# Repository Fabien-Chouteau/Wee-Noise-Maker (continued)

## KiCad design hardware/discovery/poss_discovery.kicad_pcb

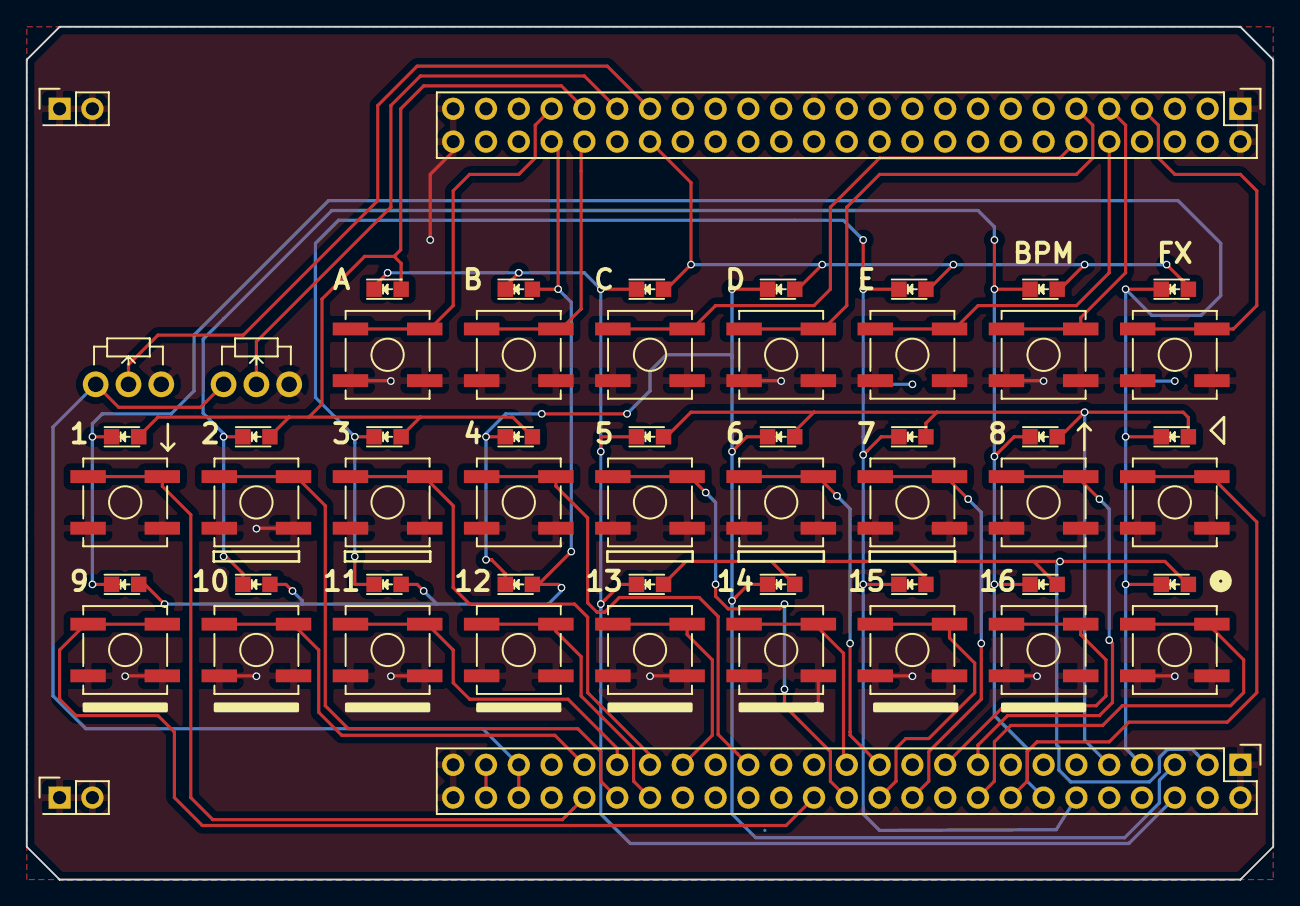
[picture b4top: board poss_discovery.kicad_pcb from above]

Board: 2 copper layers, 96.5 x 66.0 mm, 56 parts (0 on the bottom side), 41 nets.

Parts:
D1, D2, D3, D4, D5, D6, D7, D8, D9, D10, D11, D12, D13, D14, D15, D16, D17, D18, D19, D20, D21, D22, D23, D24, D25: LED; LED_0805
J1, J5: HEADER_2; Pin_Header_Straight_2x01
J2, J3: HEADER_25x2; Pin_Header_Straight_2x25
Play1, Play2: SW_PUSH; SW_SPST_B3SL-1002P
RV1, RV2: POT; Potentiometer_WirePads_Small
SW1, SW2, SW3, SW4, SW5, SW6, SW7, SW8, SW9, SW10, SW11, SW12, SW13, SW14, SW15, SW16, SW17, SW18, SW19, SW20, SW21, SW22: SW_PUSH; SW_SPST_B3SL-1002P
Write1: SW_PUSH; SW_SPST_B3SL-1002P

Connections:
/3V: J3.45, J3.46, RV1.1, RV2.1
/5V: J3.47, J3.48
/B1: J3.42, SW1.1
/B2: J3.40, SW2.1
/B3: J3.37, SW3.1
/B4: J3.31, SW4.1
/B5: J3.26, SW5.1
/B6: J3.23, SW6.1
/B7: J3.22, SW7.1
/B8: J3.17, SW8.1
/B9: J3.28, SW9.1
/B10: J3.41, SW10.1
/B11: J3.39, SW11.1
/B12: J3.38, SW12.1
/B13: J3.35, SW13.1
/B14: J3.25, SW14.1
/B15: J3.24, SW15.1
/B16: J3.19, SW16.1
/BF1: J2.43, SW17.1
/BF2: J2.42, SW18.1
/BF3: J2.12, SW19.1
/BF4: J2.11, SW20.1
/BF5: J2.10, SW21.1
/BPM: J2.9, SW22.1
/COL1: D1.2, D2.2, D3.2, D4.2, D5.2, J3.3
/COL2: D6.2, D7.2, D8.2, D9.2, D10.2, J3.9
/COL3: D11.2, D12.2, D13.2, D14.2, D15.2, J2.38
/COL4: D16.2, D17.2, D18.2, D19.2, D20.2, J2.41
/COL5: D21.2, D22.2, D23.2, D24.2, D25.2, J2.44
/FX: J2.7, Play2.1
/GND: J1.1, J1.2, J2.1, J2.2, J2.27, J2.45, J2.49, J2.50, J3.1, J3.2, J3.49, J3.50, J5.1, J5.2, Play1.2, Play2.2, RV1.3, RV2.3, SW1.2, SW2.2, SW3.2, SW4.2, SW5.2, SW6.2, SW7.2, SW8.2, SW9.2, SW10.2, SW11.2, SW12.2, SW13.2, SW14.2, SW15.2, SW16.2, SW17.2, SW18.2, SW19.2, SW20.2, SW21.2, SW22.2, Write1.2
/PA1: J2.39, RV1.2
/PA3: J2.37, RV2.2
/PA8: D5.1, D10.1, D15.1, D20.1, D25.1, J3.7
/PA15: D3.1, D8.1, D13.1, D18.1, D23.1, J3.12
/PC8: D2.1, D7.1, D12.1, D17.1, D22.1, J3.5
/PC9: D1.1, D6.1, D11.1, D16.1, D21.1, J3.6
/PC11: D4.1, D9.1, D14.1, D19.1, D24.1, J3.14
/PD0: J3.16, Play1.1
/PD2: J3.18, Write1.1
/VDD: J2.47, J2.48

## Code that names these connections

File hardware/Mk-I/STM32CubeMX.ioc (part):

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Mcu.Name=STM32F437V(G-I)Tx
Mcu.Package=LQFP100
Mcu.UserName=STM32F437VITx
PA0/WKUP.Mode=SYS-WakeUp
PA0/WKUP.Signal=SYS_WKUP
PA1.Signal=S_TIM2_CH2
PA10.Signal=GPIO_Input
PA11.Mode=Device_Only
PA11.Signal=USB_OTG_FS_DM
PA12.Mode=Device_Only
PA12.Signal=USB_OTG_FS_DP
PA13.Mode=Serial-Wire
PA13.Signal=SYS_JTMS-SWDIO
PA14.Mode=Serial-Wire
PA14.Signal=SYS_JTCK-SWCLK
PA15.Mode=Full_Duplex_Master
PA15.Signal=I2S3_WS
PA2.Signal=GPIO_Input
PA3.Signal=GPIO_Input
PA4.Signal=GPIO_Output
PA5.Signal=S_TIM2_CH1_ETR
PA6.Signal=S_TIM3_CH1
PA7.Signal=S_TIM3_CH2
PA9.Signal=USB_OTG_FS_VBUS
PB0.Signal=GPIO_Output
PB1.Signal=GPIO_Input
PB10.Signal=GPIO_Input
PB11.Signal=GPIO_Output
PB12.Signal=GPIO_Input
PB13.Signal=GPIO_Input
PB14.Signal=GPIO_Input
PB15.Signal=GPIO_Output
PB3.Mode=Full_Duplex_Master
PB3.Signal=I2S3_CK
PB4.Mode=Full_Duplex_Master
PB4.Signal=I2S3_ext_SD
PB5.Mode=Full_Duplex_Master
PB5.Signal=I2S3_SD
PB6.Mode=I2C
PB6.Signal=I2C1_SCL
PB7.Mode=I2C
PB7.Signal=I2C1_SDA
PC0.Signal=GPIO_Output
PC1.Signal=GPIO_Input
PC10.Mode=mmc_4_bits_Wide_bus
PC10.Signal=SDIO_D2
PC11.Mode=mmc_4_bits_Wide_bus
PC11.Signal=SDIO_D3
PC12.Mode=mmc_4_bits_Wide_bus
PC12.Signal=SDIO_CK
PC14/OSC32_IN.Signal=GPIO_Input
PC15/OSC32_OUT.Signal=GPIO_Input
PC2.Signal=GPIO_Output
PC3.Signal=GPIO_Input
PC4.Signal=GPIO_Input
PC5.Signal=GPIO_Input
PC6.Signal=GPIO_Input
PC7.Mode=Master_Clock_Activated
PC7.Signal=I2S3_MCK
PC8.Mode=mmc_4_bits_Wide_bus
PC8.Signal=SDIO_D0
PC9.Mode=mmc_4_bits_Wide_bus
PC9.Signal=SDIO_D1
PD10.Signal=GPIO_Input
PD11.Signal=GPIO_Output
PD12.Signal=GPIO_Output
PD13.Signal=GPIO_Output
PD14.Signal=GPIO_Output
PD15.Signal=GPIO_Input
PD2.Mode=mmc_4_bits_Wide_bus
PD2.Signal=SDIO_CMD
PD8.Signal=GPIO_Input
PD9.Signal=GPIO_Input
PE10.Signal=GPIO_Input
PE11.Signal=GPIO_Input
PE12.Signal=GPIO_Input
PE13.Signal=GPIO_Output
PE14.Signal=GPIO_Input
PE15.Signal=GPIO_Input
PE7.Signal=GPIO_Input
PE8.Signal=GPIO_Input
PE9.Signal=GPIO_Output
PH0/OSC_IN.Mode=HSE-External-Oscillator
PH0/OSC_IN.Signal=RCC_OSC_IN
PH1/OSC_OUT.Mode=HSE-External-Oscillator
PH1/OSC_OUT.Signal=RCC_OSC_OUT
RCC.HSEState-ClockTree=RCC_HSE_ON
RCC.HSE_VALUE=25000000
RCC.SYSCLKFreq_VALUE=16000000

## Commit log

2016-12-11 Add first version of the discovery
2016-12-21 Add known problems to the RevA schematics
2016-12-21 Start RevB of the discovery board
    - Fix RevA known problems
    - Custom scheme and footprint for the headers
    - Improved silkscreen
2016-12-21 Discovery: Start power section
2016-12-21 Discovery: add the MCU
2016-12-21 Discovery: Fix channel button labels
2016-12-21 Discovery: Fix volume symbol
2016-12-21 Improve SMD version of the discovery headers
2016-12-23 Discovery start power section
2016-12-23 Discovery: switch to a 9x3 LED matrix to simplify the PCB layout
2016-12-23 Discovery: SMT2F4 grounding
2016-12-23 Discovery: Fix battery connector orientation
2016-12-23 Discovery: Start audio schematic
2016-12-23 Software: Add first prototype of SW for RevA board
2016-12-24 Discovery: Add audio DAC
2016-12-24 Discovery: Connect all button to the wakeup pin
2016-12-25 Discovery: add crystal
2016-12-25 Discovery: improve LED/button matrix layout
2016-12-27 Discovery: STM32F4 power a filtering
2016-12-27 Discovery: Fix pull-ups and add LED current limiters
2016-12-27 Discovery: Start routing LEDs and buttons
2016-12-27 Discovery LEDs and button routing part 2
2016-12-28 Discovery: Add micro SD card
2016-12-28 Discovery: End of LEDs and buttons routing
2016-12-28 Discovery: Add audio jacks
2016-12-28 Discovery: Move SD card socket
2016-12-28 Discovery: finish power routing
2016-12-28 Discovery: Add OLED screen
2016-12-29 Discovery: Add two encoders and remove the BPM button
    BPM and volume will be changed with a long press of the play button and
    the encoders
2016-12-30 Discovery: Add encoders noise filtering
2016-12-31 Discovery: Add debug port and adjust screen position
2017-01-01 Discovery: relocation of screen capa and resistor
2017-01-01 Discovery: Move the screen to the right
    and put on connector on the front side.
2017-01-01 Discovery: Connect VBAT to the MCU
2017-01-01 Discovery: Increase all components ref to 0.8 font size
2017-01-01 Discovery: Update TODO list
2017-01-01 Discovery: A couple of iimprovements in layout
2017-01-01 Split Discovery edition and stand alone (Mk-I)
2017-01-01 Discovery: Restart from RevA
2017-01-01 Discovery: Use shared components and footprints
2017-01-02 Move LED matrix scanning to an timer interrupt
    instead of a task.
2017-01-02 Remove unused suspension object
2017-01-05 Add SJ3523 audio jack footprint
2017-01-05 MK-I : Decrease mask clearance to ~3mil
2017-01-05 Try footprint of PEC11S SMT encoders
    The profile is low (14mm) but the foot print is too big (18x12mm).
2017-01-05 Mk-I: A couple of fixes in silkscreen
2017-01-05 Use encoder 3D models with the PCB design
2017-01-05 Add encoder 3D models
2017-01-07 Update TODO list
2017-01-07 Rename project: Wee Noise Maker!
2017-01-07 Move battery connector to make room for the logo
2017-01-07 Trying some logo designs
2017-01-07 Fix GND connection
2017-01-07 Update page layouts
2017-01-08 Cleanup schematics
2017-01-08 Fix VBUS track width
2017-01-08 Update project name in the software
2017-01-08 Add mounting hole
2017-01-10 HW: Fix path to 3D model
2017-01-10 HW: Hide mounting hole silkscreen ref
2017-01-10 HW: Change most of signal traces to 0.16mm
2017-01-10 HW: Add a DFU mode switch
2017-01-14 HW: Minor improvement in PCB rounting
2017-01-15 HW: Update discovery with new UI design (encoders, screen, buttons layout)
2017-01-15 HW: Update TODO list
2017-01-15 HW: Add discovery Rev-A schematics PDF
2017-01-15 HW: Add screen reset line and some ground path tweaking
2017-01-15 HW: Use a different MCU pins for the discovery board
    This simplifies the PCB layout.
2017-01-15 HW:Update revision of the discovery board
2017-01-15 HW: Remove useless reference on discovery board
2017-01-15 HW: Discovery Rev B
2017-01-15 HW: Wee Noise Maker Mk-I Rev B
2017-01-16 HW: Crank knob for the EC12D encoders
2017-01-17 HW: fix know and crank 3D models
2017-01-22 Fix exposed crystal trace by R6 pad mask
2017-01-22 Set theme jekyll-theme-time-machine
2017-01-22 Start GitHub page
2017-01-22 Media: Add few pictures of the disco rev-A
2017-01-22 Add first blog entry
2017-01-22 Blog: Fix video link
2017-01-22 Media: Remove the script logo
2017-01-22 Media: Add two logo rendering
2017-01-22 Blog: Add the logo
2017-01-24 Move media/ in docs/
2017-01-30 SW: Change project file name
2017-01-30 Media: Add a 3D render of MK1 Rev-A
2017-01-30 Blog post #2
2017-01-30 docs/index.md: typo...
2017-03-06 HW: known problems cont.
2017-03-06 HW: Add revision text
2017-03-06 HW: Improving ground again
2017-03-06 HW: Start Mk-I rev-A known problems
2017-03-06 HW: Fix encoders footprint
2017-03-06 Add picture of new boards
2017-03-06 HW: Fix regulator footprint
2017-03-06 HW: Fix DAC coupling caps
2017-03-06 HW: Use filled white boxes for all keyboard keys
2017-03-06 Bump ADL version
2017-03-06 HW: Improve regulator footprint
2017-03-06 HW: Improve ground layout
2017-03-11 HW: Add I2C debug/extension connector
2017-03-11 HW: Improve oscillator layout
2017-03-12 HW: Divide VBAT before connecting to the MCU
2017-03-12 HW: Increase board size
2017-03-18 HW: Mk-I rev-B
2017-03-19 HW: Add rev-B BOM
2017-04-08 HW: Start rev-C with DAC VDDD fix
2017-04-09 HW: A couple of improvements in layout and ground
2017-04-18 HW: Enlarge screen footprint
    To give room for more models.
2017-04-22 Add Giza submodule
2017-04-22 Add encoder support
2017-04-22 Add I2C init package
2017-04-22 Add screen package
2017-04-22 Update Giza
2017-04-22 Add bitmap assets and conversion
2017-04-22 Update IOs to Mk-I rev-B
2017-05-08 Add a screen emulation project to ease dev of the GUI
2017-05-08 Start GUI module
2017-05-08 Check-in generated bitmap data
2017-05-08 Add .gitignore in screen emulator obj dir
2017-05-08 HW: Mk-I rev-C
2017-07-02 README: Badges!
2017-07-02 Update blog with 3rd entry
2017-07-02 Update blog with 4th entry
2017-07-06 Update Ada_Drivers_Library
2017-07-22 WNM.Audio_DAC
2017-07-22 Start Audio_DAC package
2017-07-22 Update screen emulation for new bitmap API
2017-07-22 Adjust priorities
2017-07-22 WNM.Audio_DAC: Minor update
2017-07-22 WNM.UI: Set volume and BPM with encoders
2017-07-22 Enable I2S input
2017-07-22 WNM.I2C: Use DMA for TX
2017-07-22 Just saving this piece of code
2017-07-22 WNM.Screen: Update for new API
2017-07-22 Media: Add Mk-I rev-C pictures
2017-07-23 WNM: Increase UI task period
2017-07-23 WNM.SDCard: Add SD card HW initialization
2017-07-23 First working sequencer
2017-07-23 Mute and unmute channels with the FX mode
2017-07-23 Fix direct play
2017-07-23 Start MIDI package
2017-07-23 Add solo mode FX
2017-07-23 Rename Channels to Tracks
    To avoid confusion with MIDI channels
2017-07-23 HW: Update parts value
2017-07-23 Improve BPM handling
2017-07-23 Move encoders handling to the UI task
2017-07-23 Reorg screen and GUI
2017-08-06 Add generic FIFO implementation
2017-08-06 Start buffer handling
2017-08-06 Start sample streams
2017-08-18 WNM.GUI: Start parameters
2017-08-18 Start pattern sequencer
2017-08-18 Start track panning
2017-08-18 WNM.Sequencer: Refactor to remove task
    The sequencer is now executed in the UI task
2017-08-18 WNM.UI: Fix primary stack and secondary stack size
2017-08-18 WNM.SDCard: Mount the SDCard with File_IO
2017-08-18 WNM.Sample_Stream: Increase sample capacity
2017-08-18 Main: Init SDCard and sample stream
2017-08-18 Quick_Synth: Change the way synth note stops
2017-08-19 Tentative switch to a different input paradigm
    Sample pattern editing is now the main mode.
2017-08-19 Introduce conditional triggers
2017-08-19 Fix LED showing step progress
2017-08-19 WNM.GUI: Improve inverted text drawing
2017-08-27 Create a script to format the sdcard
2017-08-27 WNM.Sample_Stream: Start recording system
2017-08-27 Start sample library package
2017-08-27 Fix 5x7 font
2017-08-27 Start messing around with menus...
2017-09-02 WNM.GUI.Bitmap_Font: Keep render within 7 pixel height
2017-09-02 WNM.GUI.Menu.Text_Dialog: Improve text edit
2017-09-02 WNM.GUI.Menu.Drawing: Fix source color
2017-09-02 WNM.GUI.Menu.Sample_Select: Change interface
2017-09-02 Add root menu package
2017-09-02 Switch from stereo to mono samples
2017-09-02 Add per track mute control
2017-09-02 WNM.UI: Revert previous LED patch but keep the brightness levels
2017-09-02 Add per track volume control
2017-09-02 WNM.Pattern_Sequencer: Add a function to know if a pattern is part of the sequence
2017-09-02 WNM.UI: Turn on LEDs by row (failed experiment)
    ...instead of one by one.
    The idea was to have less interrupts by handling all the LEDs in the
    same raw at the same time.
    In practice,powering multiple LEDs at the same time is not great as they
    will not have the same brightness, especially when the LEDs are not of
    the same color.
2017-09-02 Move LED handling to a separate package
2017-09-24 WNM.SDCard: Add a monitor for debugging
2017-09-24 WNM.Sample_Stream: Add support for the create sample feature
2017-09-24 WNM.Screen: Add an option to invert the color of a BMP
2017-09-24 WNM.GUI.Menu: Start the Create sample menu
2017-09-24 .gitignore: *.stderr *.stdout
2017-09-24 Quick_Synth: Improve support for sample recording
2017-09-28 WNM.GUI.Menu.Create_Sample: Copy the new sample in the user dir
2017-09-28 WNM.Sample_Library: Add a function to register a user sample after loading
2017-09-28 WNM.UI: Stop the blinking of the record/edit LED
    The play LED is already blinking so this is just extra "noise".
2017-09-28 Quick_Synth: Add a procedure to assign a sample to a track
2017-09-28 WNM.GUI.Menu.Create_Sample: Implement the assign to track feature
2017-10-14 WNM.GUI: Disaplay track number and sample name
2017-10-14 WNM.Audio_DAC: Create mono and stereo buffer types
2017-10-14 WNM.Sequencer: Create a copy pattern feature
2017-10-21 WNM.Sequencer: Bring back the sequencer task
2017-10-21 HW: TODO list for the next revision
2017-10-21 HW: Change crystal for a smd package
2017-10-21 HW: Change battery connector to SMD
2017-10-21 HW: Major change of layout...
2017-10-21 HW: Change micro SD card slot
2017-10-22 HW: Use folded foot print for the OLED screen
2017-10-22 HW: Add 3D models
2017-10-22 HW: Add missing schematic
2017-10-22 HW: Change 3.5 socket and put them on top
2017-10-28 HW: Finish rev-D layout
2017-10-29 HW: rev D production files
2017-11-25 Update for HW rev-D
2017-12-03 Refactoring button handling in a separate package
2017-12-03 WNM.GUI.Menu: Add Track_Settings window
2017-12-03 WNM.Sequencer: Also reset the step counter when entering Edit and Play_and_Edit state
2017-12-03 WNM.GUI.Update: Change information displayed for some modes
2017-12-03 WNM.UI: Remove encoder value multiplication
    With the latest hardware with don't need to that anymore, because the
    encoder signals are clean.
2017-12-03 WNM.Battery: Start a battery monitoring package
2017-12-03 WNM.Sequencer: Execute steps only when we are in a play mode
2017-12-03 WNM.Encoders: Move hardware specific declartions to the body
2017-12-03 Minor reformating
2017-12-03 WNM.Power_Control: Start power control package
2021-01-06 Reboot?
2021-01-10 Cont.
2021-02-24 Wee Noise Maker Feather proto
2021-05-18 Start MIDI sequencing
2021-05-24 Switch MIDI out to DMA
2021-09-10 Switch simulator to SFML
2021-09-10 Add sequence copy system and popups
2021-09-11 Simpler sound, better UI and GUI
2021-09-15 GUI update cont.
2021-10-22 Start RP2040 version
2021-10-25 Microsecond time and PIO rotary encoders
2021-10-25 MIDI out
2021-11-03 Revamp sequencing workflow
2021-11-04 MIDI CC labels and built-in instruments
2021-11-06 Start chord sequencer
2021-11-11 Add chord progression editor...
    and other minor stuff
2021-11-16 Add arpeggiator
2022-03-26 Start project save/load
    And a bunch of other small things...
2022-04-09 Add simple tool to build WNM ROM image
